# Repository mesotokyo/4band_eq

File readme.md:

# mini 4 band equalizer PCB

mini-size 4band equalizer PCB.

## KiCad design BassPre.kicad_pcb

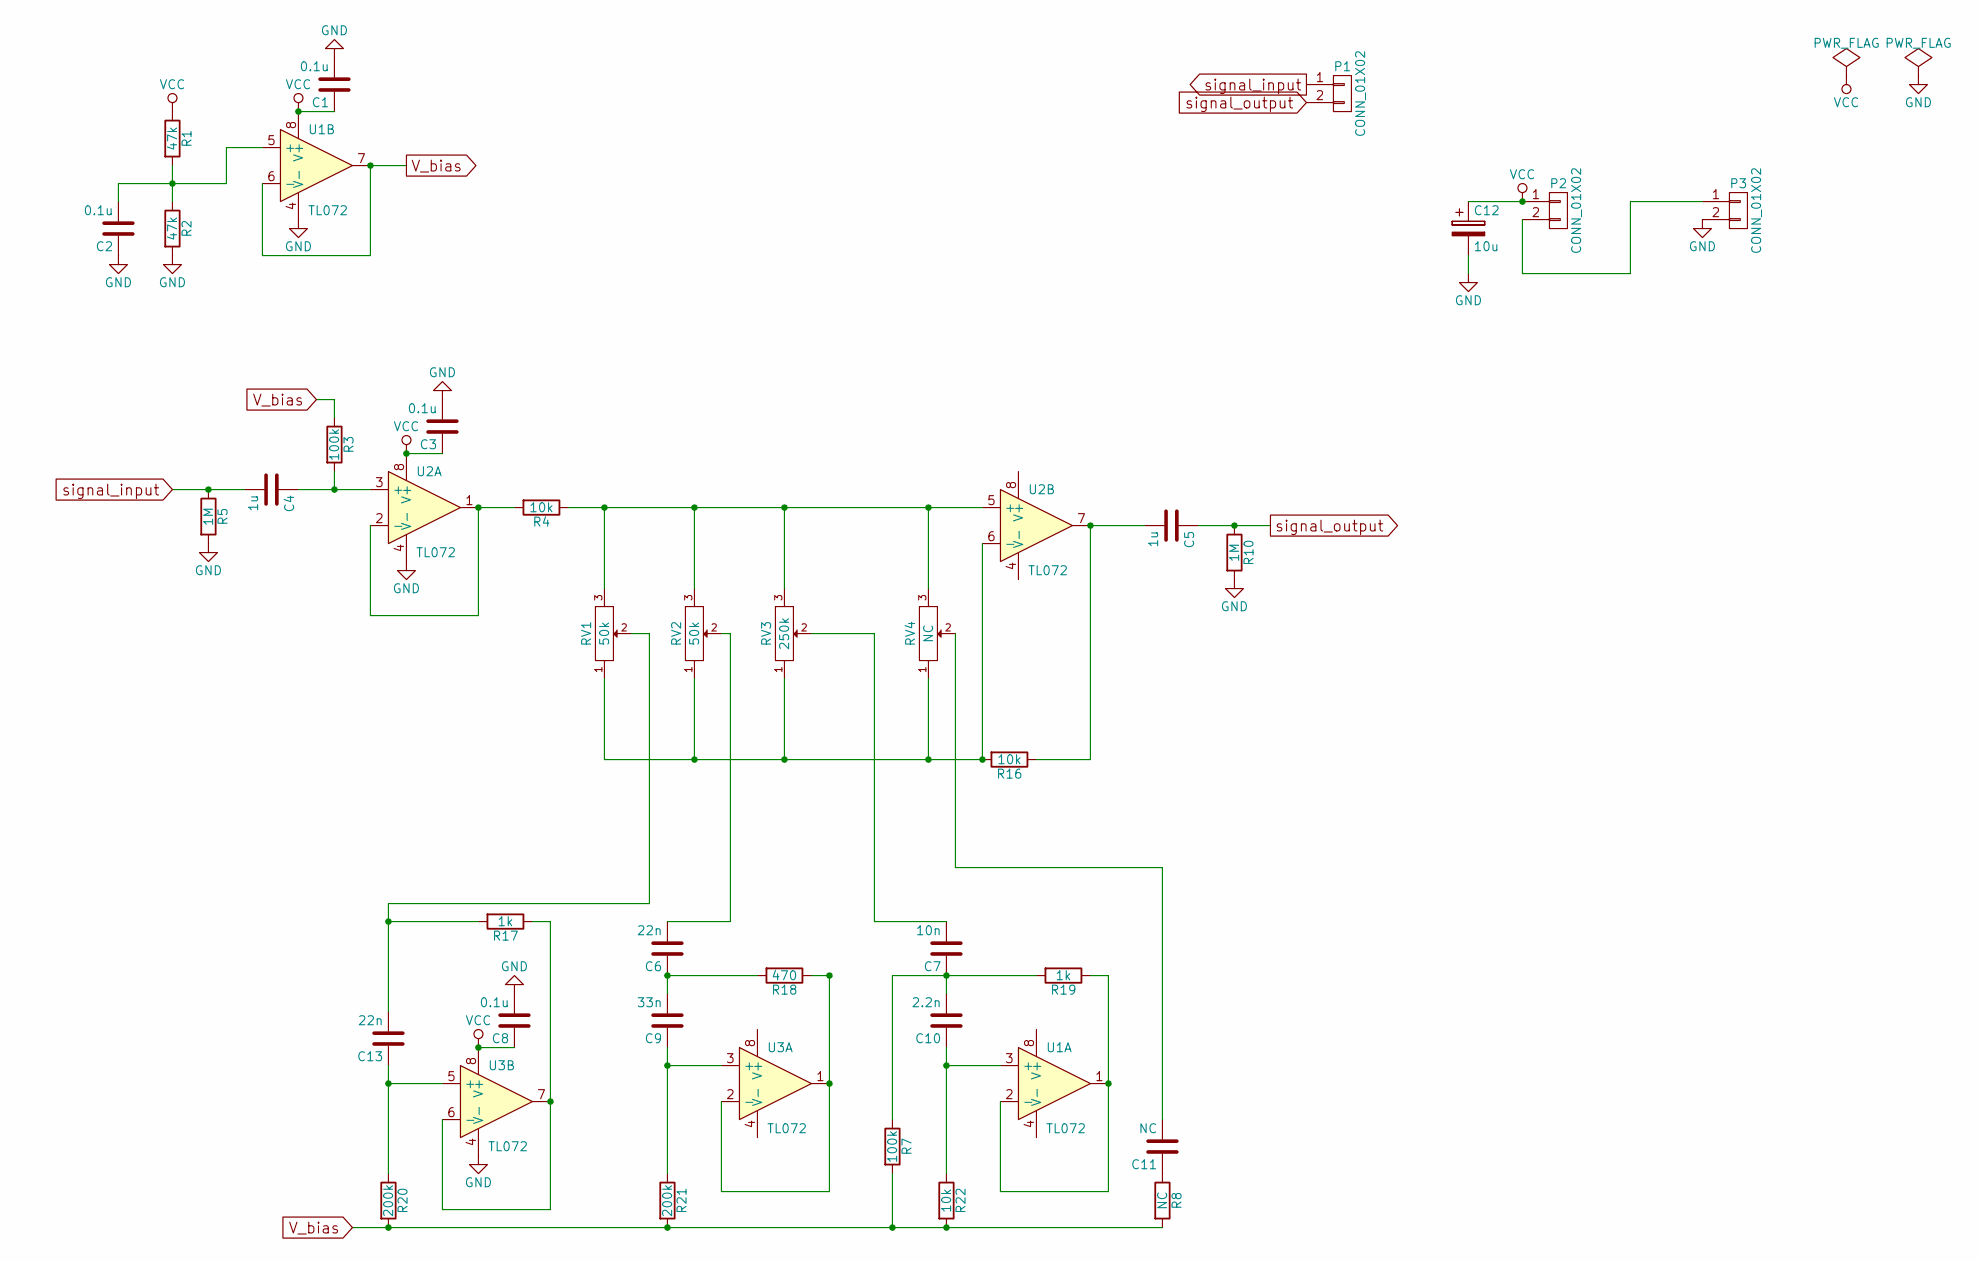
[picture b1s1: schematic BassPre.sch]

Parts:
C1, C2, C3, C8: 0.1u; C_0805_HandSoldering
C4, C5: 1u; C_1206_HandSoldering
C6, C13: 22n; C_Rect_L7.0mm_W2.5mm_P5.00mm
C7: 10n; C_Rect_L7.0mm_W2.5mm_P5.00mm
C9: 33n; C_Rect_L7.0mm_W2.5mm_P5.00mm
C10: 2.2n; C_Rect_L7.0mm_W2.5mm_P5.00mm
C11: NC; C_Rect_L7.0mm_W2.5mm_P5.00mm
C12: 10u; CP_Elec_5x5.3
P1, P2, P3: CONN_01X02; Pin_Header_Straight_1x02_Pitch2.54mm
R1, R2: 47k; R_0805_HandSoldering
R3: 100k; R_0805_HandSoldering
R4, R16, R22: 10k; R_Axial_DIN0207_L6.3mm_D2.5mm_P7.62mm_Horizontal
R5, R10: 1M; R_0805_HandSoldering
R7: 100k; R_Axial_DIN0207_L6.3mm_D2.5mm_P7.62mm_Horizontal
R8: NC; R_Axial_DIN0207_L6.3mm_D2.5mm_P7.62mm_Horizontal
R17, R19: 1k; R_Axial_DIN0207_L6.3mm_D2.5mm_P7.62mm_Horizontal
R18: 470; R_Axial_DIN0207_L6.3mm_D2.5mm_P7.62mm_Horizontal
R20, R21: 200k; R_Axial_DIN0207_L6.3mm_D2.5mm_P7.62mm_Horizontal
RV1, RV2: 50k; Pin_Header_Straight_1x03_Pitch2.54mm
RV3: 250k; Pin_Header_Straight_1x03_Pitch2.54mm
RV4: NC; Pin_Header_Straight_1x03_Pitch2.54mm
U1, U2, U3: TL072; DIP-8_W7.62mm_Socket

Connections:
GND: C1.2, C2.1, C3.2, C8.2, C12.2, P3.2, R2.2, R5.2, R10.2, U1.4 (V-), U2.4 (V-), U3.4 (V-)
unnamed: C2.2, R1.2, R2.1, U1.5 (+)
unnamed: C4.1, R3.2, U2.3 (+)
unnamed: C5.2, R16.1, U2.7
unnamed: C6.1, C9.2, R18.2
unnamed: C6.2, RV2.2
unnamed: C7.2, RV3.2
unnamed: C9.1, R21.1, U3.3 (+)
unnamed: C10.1, R22.1, U1.3 (+)
unnamed: C7.1, C10.2, R7.1, R19.2
unnamed: C11.1, R8.1
unnamed: C11.2, RV4.2
unnamed: C13.1, R20.1, U3.5 (+)
unnamed: C13.2, R17.2, RV1.2
unnamed: P2.2, P3.1
unnamed: R4.1, RV1.3, RV2.3, RV3.3, RV4.3, U2.5 (+)
unnamed: R4.2, U2.1, U2.2 (-)
unnamed: R16.2, RV1.1, RV2.1, RV3.1, RV4.1, U2.6 (-)
unnamed: R17.1, U3.6 (-), U3.7
unnamed: R18.1, U3.1, U3.2 (-)
unnamed: R19.1, U1.1, U1.2 (-)
VCC: C1.1, C3.1, C8.1, C12.1, P2.1, R1.1, U1.8 (V+), U2.8 (V+), U3.8 (V+)
V_bias: R3.1, R7.2, R8.2, R20.2, R21.2, R22.2, U1.6 (-), U1.7
signal_input: C4.2, P1.1, R5.1
signal_output: C5.1, P1.2, R10.1

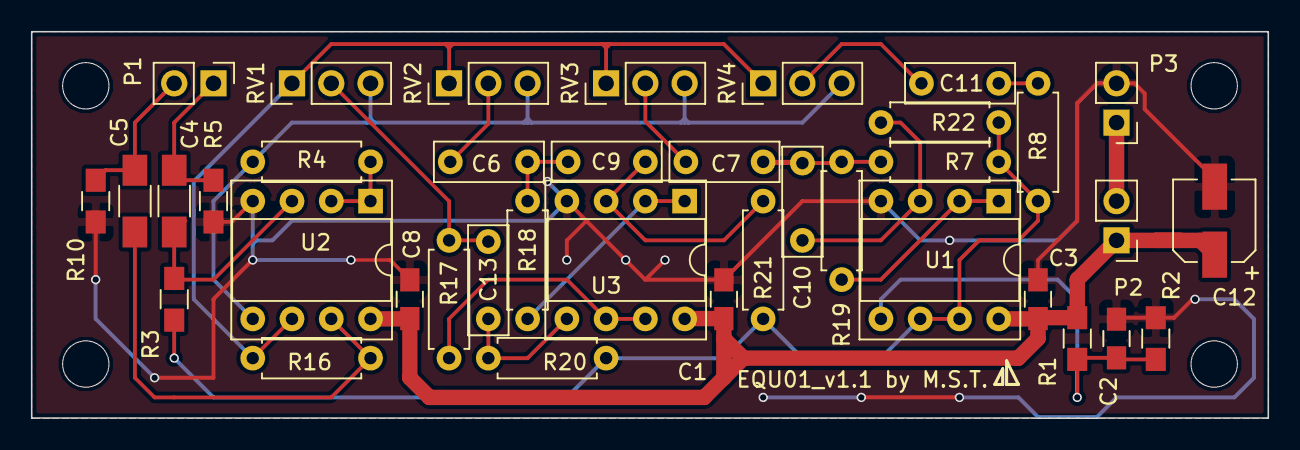
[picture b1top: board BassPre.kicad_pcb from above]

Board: 2 copper layers, 80.0 x 25.0 mm, 38 parts (0 on the bottom side), 25 nets.

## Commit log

2018-02-25 fix bypass capacitor position
2018-02-25 add license and readme
